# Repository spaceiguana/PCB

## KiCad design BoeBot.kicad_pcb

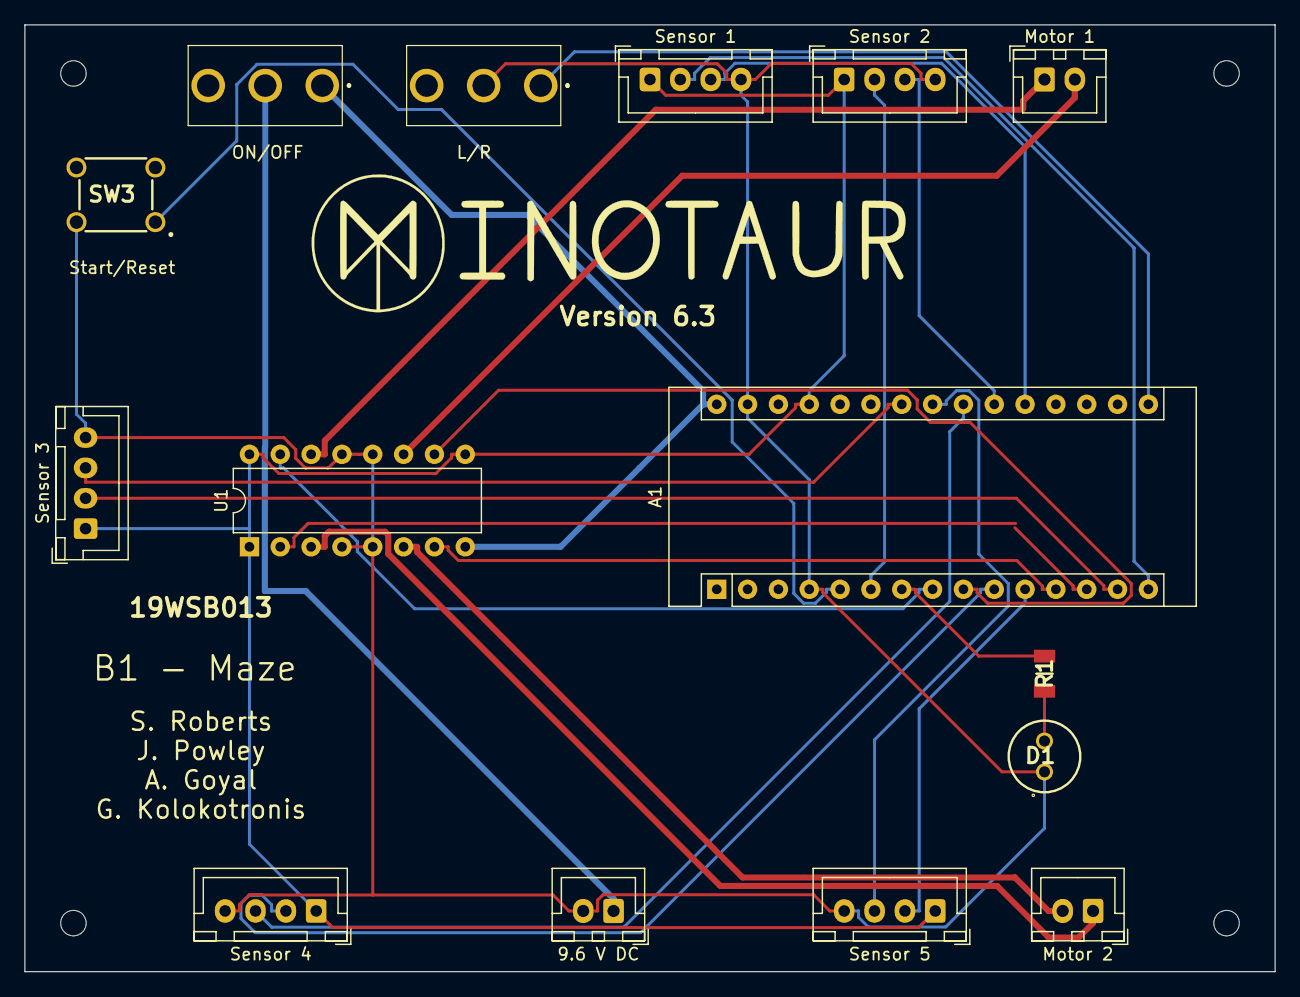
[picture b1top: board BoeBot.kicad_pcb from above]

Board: 2 copper layers, 103.0 x 78.0 mm, 19 parts (0 on the bottom side), 26 nets.

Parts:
9.6 V DC: Conn_01x02_Male; JST_XH_B2B-XH-A_1x02_P2.50mm_Vertical
A1: Arduino_Nano_v3.x; Arduino_Nano
D1: LED; L-53HD
Hole 1, Hole 2, Hole 3, Hole 4: MountingHole_2.1mm
Motor 1, Motor 2: Conn_01x02_Male; JST_XH_B2B-XH-A_1x02_P2.50mm_Vertical
R1: R; RESC3116X65N
SW1, SW2: SW_SPDT; 5MS3S402AM2QES
SW3: SW_Push; B3F1000
Sensor 1, Sensor 2, Sensor 3, Sensor 4, Sensor 5 : Conn_01x04_Male; JST_XH_B4B-XH-A_1x04_P2.50mm_Vertical
U1: L293D; DIP-16_W7.62mm

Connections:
/Echo1: A1.20, Sensor 1.3
/Echo3: A1.22, Sensor 4.3
/Echo4: A1.23, Sensor 5.3
/Echo5: A1.24, Sensor 3.3
/GND: 9.6 V DC.2, A1.4, A1.29, D1.1, SW2.2, SW3.2, Sensor 1.4, Sensor 2.4, Sensor 3.4, Sensor 4.4, Sensor 5.4, U1.4, U1.5, U1.12, U1.13
/Trig1: A1.15, Sensor 1.2
/Trig2: A1.6, Sensor 2.2
/Trig3: A1.10, Sensor 4.2
/Trig4: A1.11, Sensor 5.2
/Trig5: A1.14, Sensor 3.2
/VCC: A1.30, SW1.1, U1.8
/VCC2: A1.27, Sensor 1.1, Sensor 2.1, Sensor 3.1, Sensor 4.1, Sensor 5.1, U1.1, U1.9, U1.16
unnamed: A1.5, SW3.1
unnamed: A1.7, R1.2
unnamed: A1.8, U1.15
unnamed: A1.9, U1.10
unnamed: A1.12, U1.7
unnamed: A1.13, U1.2
unnamed: A1.16, SW2.1
unnamed: A1.21, Sensor 2.3
unnamed: D1.2, R1.1
unnamed: Motor 2.1, U1.3
unnamed: Motor 2.2, U1.6
unnamed: Motor 1.1, U1.14
unnamed: Motor 1.2, U1.11
unnamed: 9.6 V DC.1, SW1.2
